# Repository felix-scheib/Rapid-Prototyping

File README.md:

# Rapid Prototyping

This is the repository with my prototype of [Rapid Prototyping](https://obs.fbi.h-da.de/mhb/modul.php?nr=30.2670&sem=20231) by [Prof. Dr. Stefan Rapp](https://fbi.h-da.de/personen/stefan-rapp/) in the winterterm 23/24.

The following tools are used to create the prototype:

- [PlatformIO](https://platformio.org/)
- [KiCad](https://www.kicad.org/)
- [FreeCAD](https://www.freecad.org/)

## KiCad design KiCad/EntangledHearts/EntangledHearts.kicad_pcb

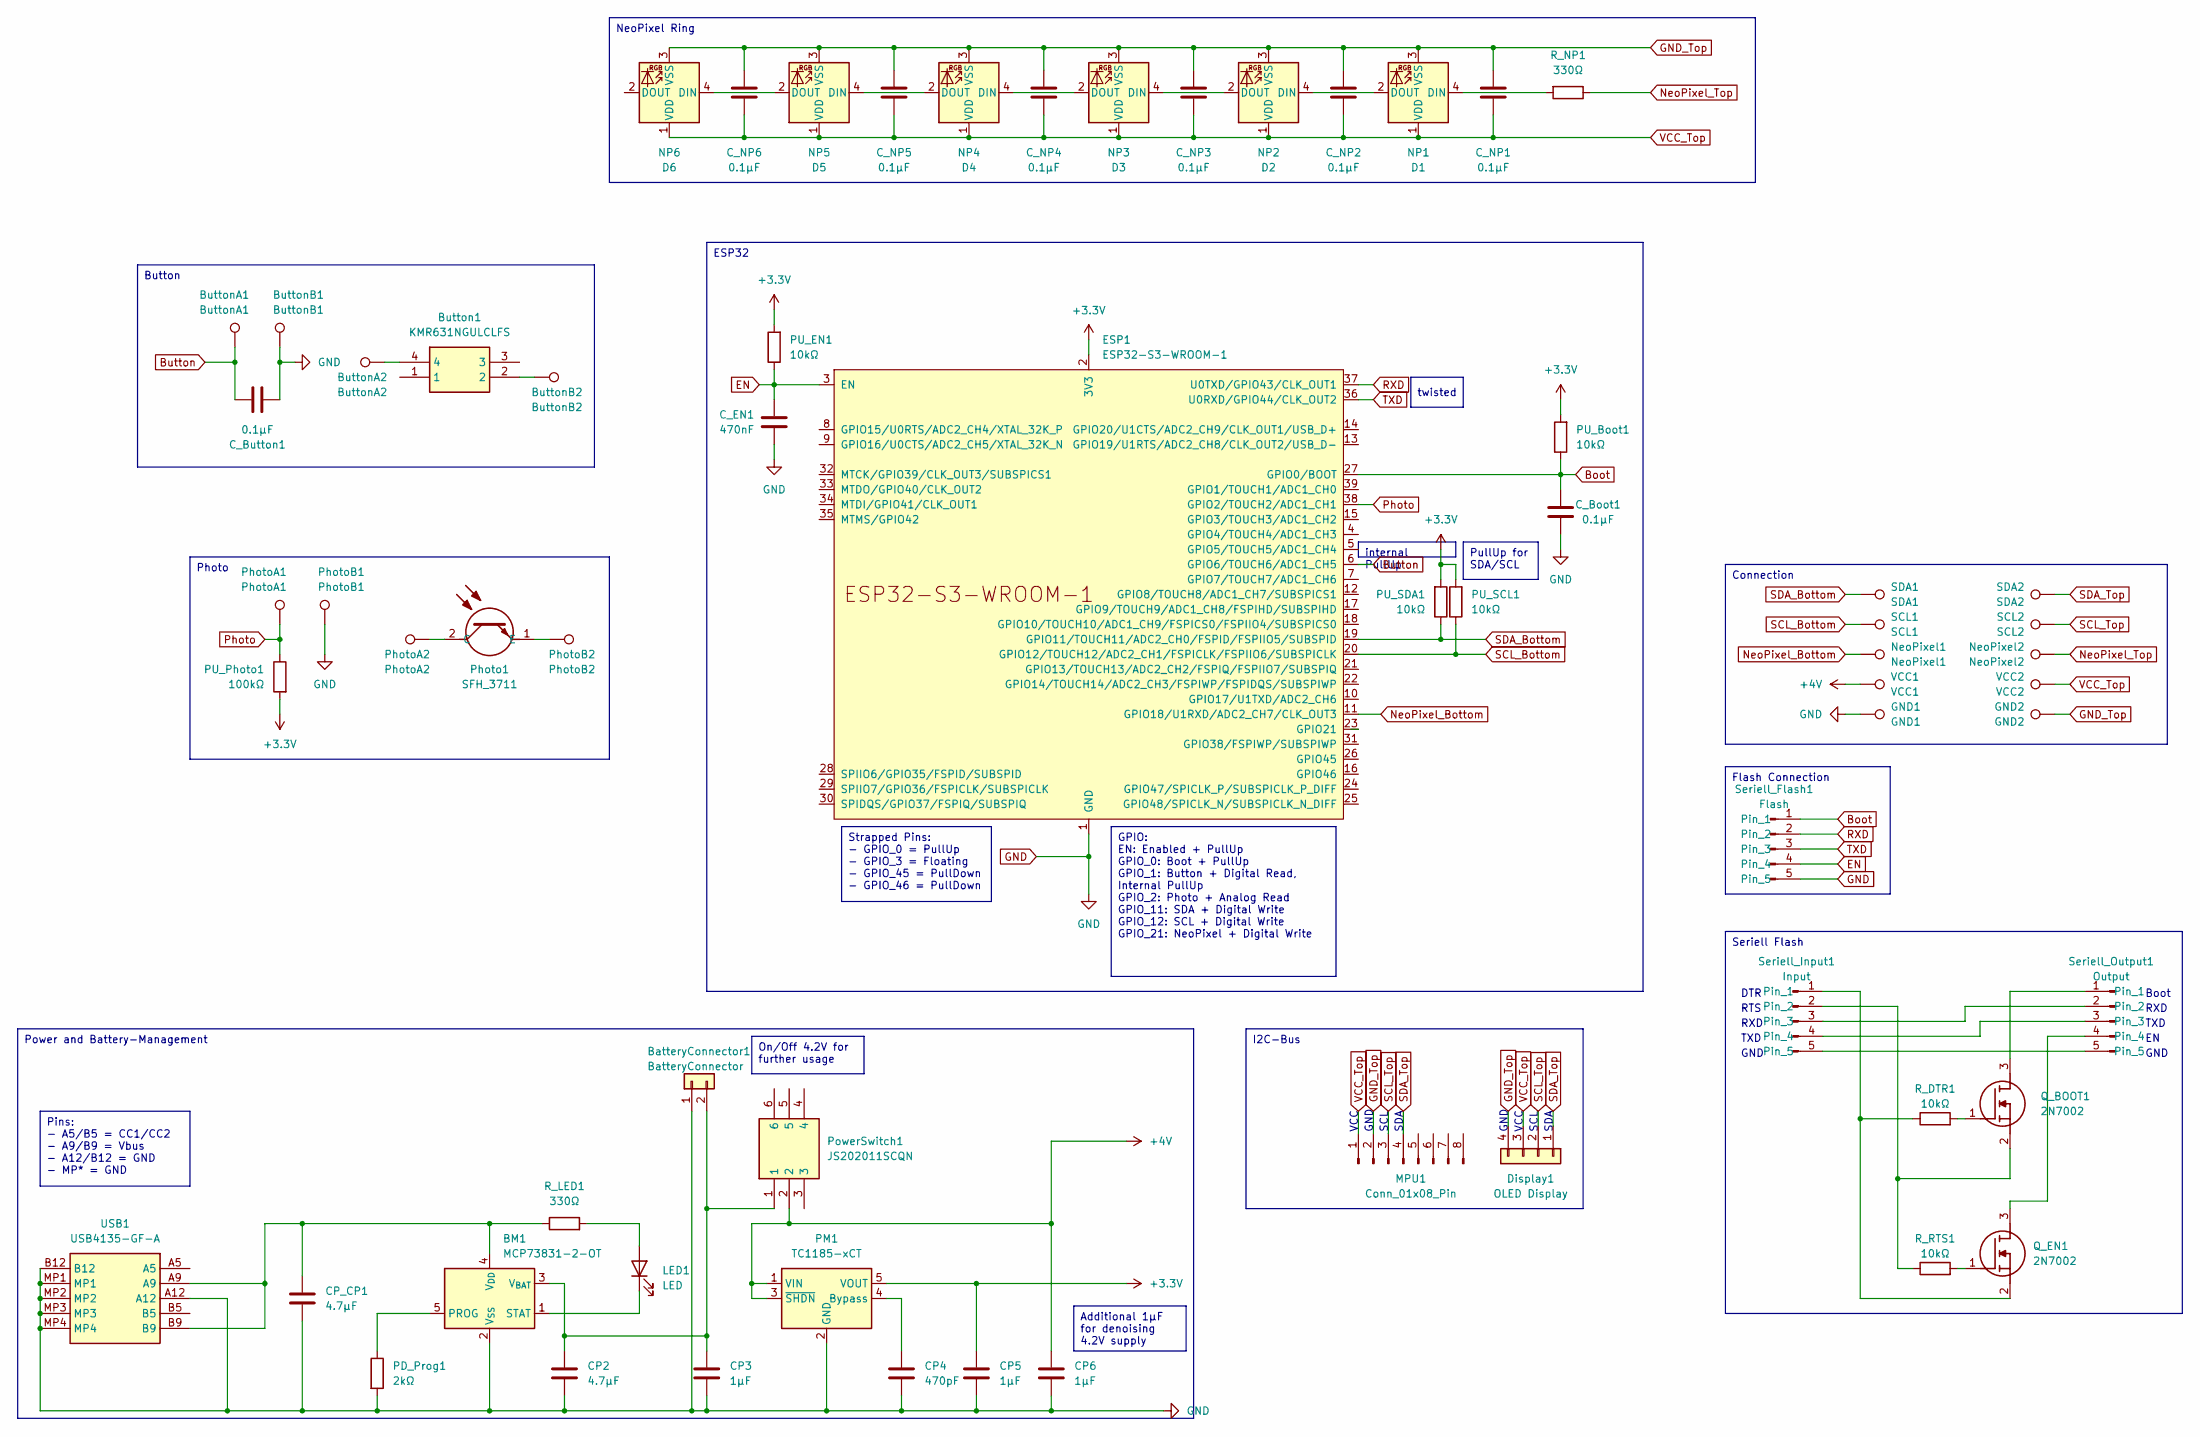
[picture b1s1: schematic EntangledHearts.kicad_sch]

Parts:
BM1: MCP73831-2-OT; SOT-23-5
BatteryConnector1: BatteryConnector; JST_PH_S2B-PH-SM4-TB_1x02-1MP_P2.00mm_Horizontal
Button1: KMR631NGULCLFS; KMR621NG; Mouser Part Number 611-KMR631NGULCLFS
ButtonA1: ButtonA1; TestPoint_Pad_1.5x1.5mm
ButtonA2: ButtonA2; TestPoint_Pad_1.5x1.5mm
ButtonB1: ButtonB1; TestPoint_Pad_1.5x1.5mm
ButtonB2: ButtonB2; TestPoint_Pad_1.5x1.5mm
CP2: 4.7µF; C_0805_2012Metric
CP3, CP5, CP6: 1µF; C_0805_2012Metric
CP4: 470pF; C_0805_2012Metric
CP_CP1: 4.7µF; C_0805_2012Metric
C_Boot1: 0.1µF; C_0805_2012Metric
C_Button1: 0.1µF; C_0805_2012Metric
C_EN1: 470nF; C_0805_2012Metric
C_NP1, C_NP2, C_NP3, C_NP4, C_NP5, C_NP6: 0.1µF; C_0805_2012Metric
D1: NP1; LED_WS2812B_PLCC4_5.0x5.0mm_P3.2mm
D2: NP2; LED_WS2812B_PLCC4_5.0x5.0mm_P3.2mm
D3: NP3; LED_WS2812B_PLCC4_5.0x5.0mm_P3.2mm
D4: NP4; LED_WS2812B_PLCC4_5.0x5.0mm_P3.2mm
D5: NP5; LED_WS2812B_PLCC4_5.0x5.0mm_P3.2mm
D6: NP6; LED_WS2812B_PLCC4_5.0x5.0mm_P3.2mm
Display1: OLED Display; PinHeader_1x04_P2.54mm_Vertical
ESP1: ESP32-S3-WROOM-1
GND1: GND1; TestPoint_Pad_1.5x1.5mm
GND2: GND2; TestPoint_Pad_1.5x1.5mm
LED1: LED; LED_0805_2012Metric
MPU1: Conn_01x08_Pin; PinHeader_1x08_P2.54mm_Vertical_SMD_Pin1Left
NeoPixel1: NeoPixel1; TestPoint_Pad_1.5x1.5mm
NeoPixel2: NeoPixel2; TestPoint_Pad_1.5x1.5mm
PD_Prog1: 2kΩ; R_0805_2012Metric
PM1: TC1185-xCT; SOT-23-5
PU_Boot1: 10kΩ; R_0805_2012Metric
PU_EN1: 10kΩ; R_0805_2012Metric
PU_Photo1: 100kΩ; R_0805_2012Metric
PU_SCL1: 10kΩ; R_0805_2012Metric
PU_SDA1: 10kΩ; R_0805_2012Metric
Photo1: SFH_3711; SFH3711; Mouser Part Number 720-SFH3711
PhotoA1: PhotoA1; TestPoint_Pad_1.5x1.5mm
PhotoA2: PhotoA2; TestPoint_Pad_1.5x1.5mm
PhotoB1: PhotoB1; TestPoint_Pad_1.5x1.5mm
PhotoB2: PhotoB2; TestPoint_Pad_1.5x1.5mm
PowerSwitch1: JS202011SCQN; Mouser Part Number 611-JS202011SCQN
Q_BOOT1: 2N7002; SOT96P240X120-3N; Manufacturer_Part_Number 2N7002; Mouser Part Number 512-2N7002
Q_EN1: 2N7002; SOT96P240X120-3N; Manufacturer_Part_Number 2N7002; Mouser Part Number 512-2N7002
R_DTR1: 10kΩ; R_0805_2012Metric
R_LED1: 330Ω; R_0805_2012Metric
R_NP1: 330Ω; R_0805_2012Metric
R_RTS1: 10kΩ; R_0805_2012Metric
SCL1: SCL1; TestPoint_Pad_1.5x1.5mm
SCL2: SCL2; TestPoint_Pad_1.5x1.5mm
SDA1: SDA1; TestPoint_Pad_1.5x1.5mm
SDA2: SDA2; TestPoint_Pad_1.5x1.5mm
Seriell_Flash1: Flash; PinHeader_1x05_P2.54mm_Vertical_SMD_Pin1Left
Seriell_Input1: Input; PinHeader_1x05_P2.54mm_Vertical_SMD_Pin1Left
Seriell_Output1: Output; PinHeader_1x05_P2.54mm_Vertical_SMD_Pin1Left
USB1: USB4135-GF-A; USB4135GFA; Mouser Part Number 640-USB4135-GF-A
VCC1: VCC1; TestPoint_Pad_1.5x1.5mm
VCC2: VCC2; TestPoint_Pad_1.5x1.5mm

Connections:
+3.3V: CP5.1, ESP1.2 (3V3), PM1.5 (VOUT), PU_Boot1.2, PU_EN1.2, PU_Photo1.2, PU_SCL1.2, PU_SDA1.2
+4V: CP6.1, PM1.1 (VIN), PM1.3 (~SHDN), PowerSwitch1.2, VCC1.1
Boot: C_Boot1.2, ESP1.27 (GPIO0/BOOT), PU_Boot1.1, Seriell_Flash1.1
Button: ButtonA1.1, C_Button1.1, ESP1.6 (GPIO6/TOUCH6/ADC1_CH5)
EN: C_EN1.2, ESP1.3 (EN), PU_EN1.1, Seriell_Flash1.4
GND: BM1.2 (V_{SS}), BatteryConnector1.1, ButtonB1.1, CP2.2, CP3.2, CP4.2, CP5.2, CP6.2, CP_CP1.2, C_Boot1.1, C_Button1.2, C_EN1.1, ESP1.1 (GND), ESP1.40 (GND), ESP1.41 (GND), GND1.1, PD_Prog1.2, PM1.2 (GND), PhotoB1.1, Seriell_Flash1.5, USB1.A12, USB1.B12, USB1.MP1, USB1.MP2, USB1.MP3, USB1.MP4
GND_Top: C_NP1.2, C_NP2.2, C_NP3.2, C_NP4.2, C_NP5.2, C_NP6.2, D1.3 (VSS), D2.3 (VSS), D3.3 (VSS), D4.3 (VSS), D5.3 (VSS), D6.3 (VSS), Display1.4, GND2.1, MPU1.2
NeoPixel_Bottom: ESP1.11 (GPIO18/U1RXD/ADC2_CH7/CLK_OUT3), NeoPixel1.1
NeoPixel_Top: NeoPixel2.1, R_NP1.1
unnamed: BM1.5 (PROG), PD_Prog1.1
unnamed: BM1.1 (STAT), LED1.1 (K)
unnamed: BM1.3 (V_{BAT}), BatteryConnector1.2, CP2.1, CP3.1, PowerSwitch1.1
unnamed: BM1.4 (V_{DD}), CP_CP1.1, R_LED1.1, USB1.A9, USB1.B9
unnamed: Button1.2, ButtonB2.1
unnamed: Button1.4, ButtonA2.1
unnamed: D1.4 (DIN), R_NP1.2
unnamed: D1.2 (DOUT), D2.4 (DIN)
unnamed: D2.2 (DOUT), D3.4 (DIN)
unnamed: D3.2 (DOUT), D4.4 (DIN)
unnamed: D4.2 (DOUT), D5.4 (DIN)
unnamed: D5.2 (DOUT), D6.4 (DIN)
unnamed: LED1.2 (A), R_LED1.2
unnamed: CP4.1, PM1.4 (Bypass)
unnamed: Photo1.2 (C), PhotoA2.1
unnamed: Photo1.1 (E), PhotoB2.1
unnamed: Q_BOOT1.3 (D), Seriell_Output1.1
unnamed: Q_BOOT1.1 (G), R_DTR1.2
unnamed: Q_BOOT1.2 (S), R_RTS1.1, Seriell_Input1.2
unnamed: Q_EN1.3 (D), Seriell_Output1.4
unnamed: Q_EN1.1 (G), R_RTS1.2
unnamed: Q_EN1.2 (S), R_DTR1.1, Seriell_Input1.1
unnamed: Seriell_Input1.3, Seriell_Output1.2
unnamed: Seriell_Input1.4, Seriell_Output1.3
unnamed: Seriell_Input1.5, Seriell_Output1.5
Photo: ESP1.38 (GPIO2/TOUCH2/ADC1_CH1), PU_Photo1.1, PhotoA1.1
RXD: ESP1.37 (U0TXD/GPIO43/CLK_OUT1), Seriell_Flash1.2
SCL_Bottom: ESP1.20 (GPIO12/TOUCH12/ADC2_CH1/FSPICLK/FSPIIO6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), PU_SCL1.1, SCL1.1
SCL_Top: Display1.2, MPU1.3, SCL2.1
SDA_Bottom: ESP1.19 (GPIO11/TOUCH11/ADC2_CH0/FSPID/FSPIIO5/S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), PU_SDA1.1, SDA1.1
SDA_Top: Display1.1, MPU1.4, SDA2.1
TXD: ESP1.36 (U0RXD/GPIO44/CLK_OUT2), Seriell_Flash1.3
VCC_Top: C_NP1.1, C_NP2.1, C_NP3.1, C_NP4.1, C_NP5.1, C_NP6.1, D1.1 (VDD), D2.1 (VDD), D3.1 (VDD), D4.1 (VDD), D5.1 (VDD), D6.1 (VDD), Display1.3, MPU1.1, VCC2.1

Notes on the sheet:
Additional 1µF for denoising 4.2V supply
Pins: - A5/B5 = CC1/CC2 - A9/B9 = Vbus - A12/B12 = GND - MP* = GND
On/Off 4.2V for further usage
Power and Battery-Management
Photo
I2C-Bus
ESP32
internal PullUp
PullUp for SDA/SCL
GPIO: EN: Enabled + PullUp GPIO_0: Boot + PullUp GPIO_1: Button + Digital Read, Internal PullUp GPIO_2: Photo + Analog Read GPIO_11: SDA + Digital Write GPIO_12: SCL + Digital Write GPIO_21: NeoPixel + Digital Write
Flash Connection
twisted
Seriell Flash
Connection
Strapped Pins: - GPIO_0 = PullUp - GPIO_3 = Floating - GPIO_45 = PullDown - GPIO_46 = PullDown
Button
NeoPixel Ring
TXD
SCL
GND
RXD
VCC
DTR
SDA
RTS
Boot

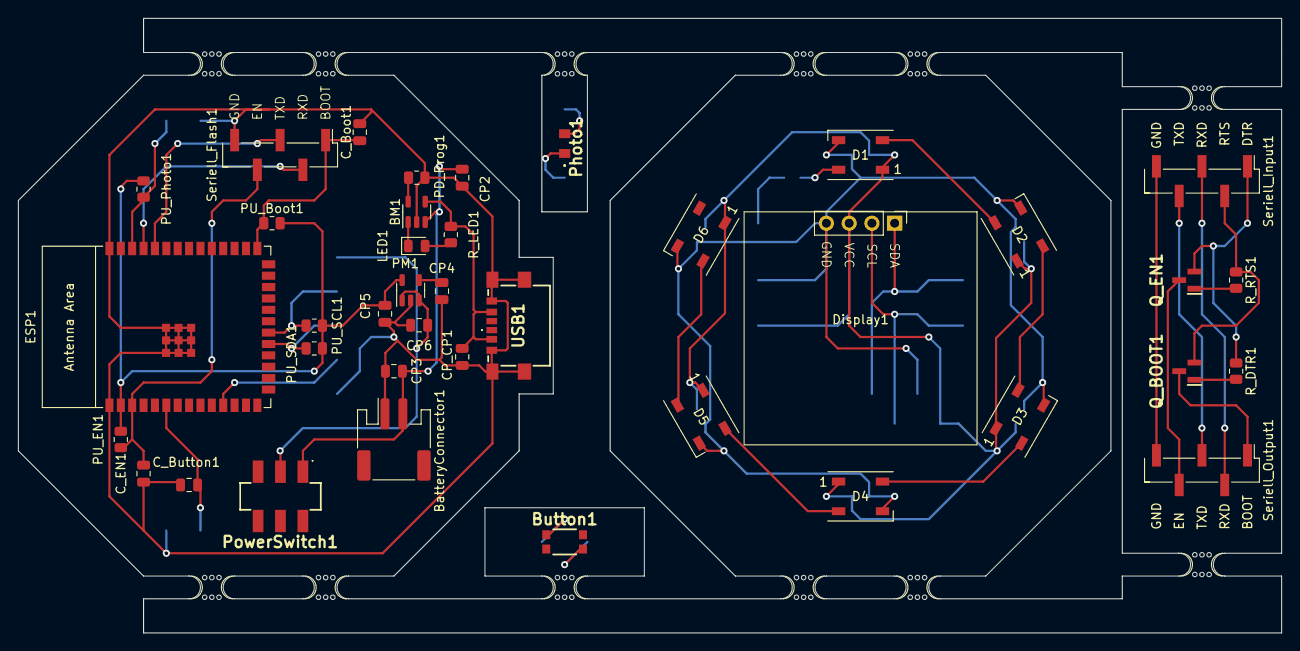
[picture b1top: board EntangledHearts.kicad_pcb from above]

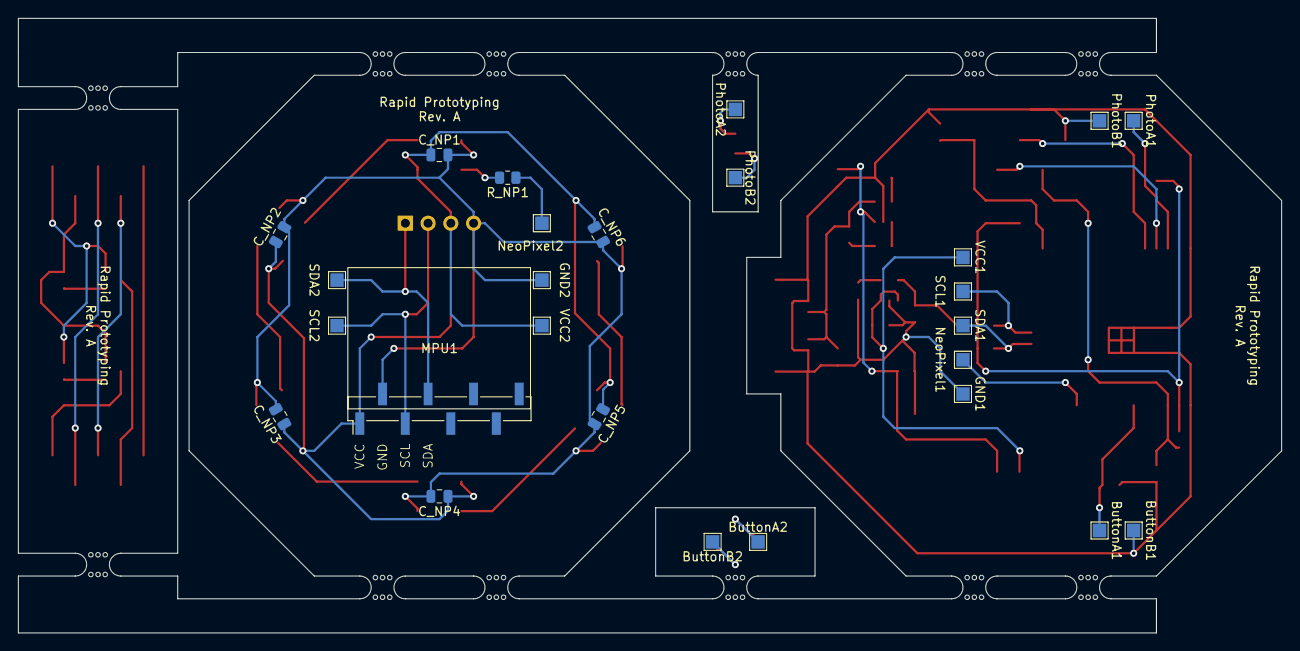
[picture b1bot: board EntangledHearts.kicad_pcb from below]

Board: 2 copper layers, 141.0 x 68.6 mm, 77 parts (26 on the bottom side), 42 nets.

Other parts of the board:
mouse-bite-2.54mm-slot, mouse-bite-2.54mm-slot#2, mouse-bite-2.54mm-slot#3, mouse-bite-2.54mm-slot#4, mouse-bite-2.54mm-slot#5, mouse-bite-2.54mm-slot#6, mouse-bite-2.54mm-slot#7, mouse-bite-2.54mm-slot#8, mouse-bite-2.54mm-slot#9, mouse-bite-2.54mm-slot#10, mouse-bite-2.54mm-slot#11, mouse-bite-2.54mm-slot#12: VAL**; mouse-bite-2.54mm-slot

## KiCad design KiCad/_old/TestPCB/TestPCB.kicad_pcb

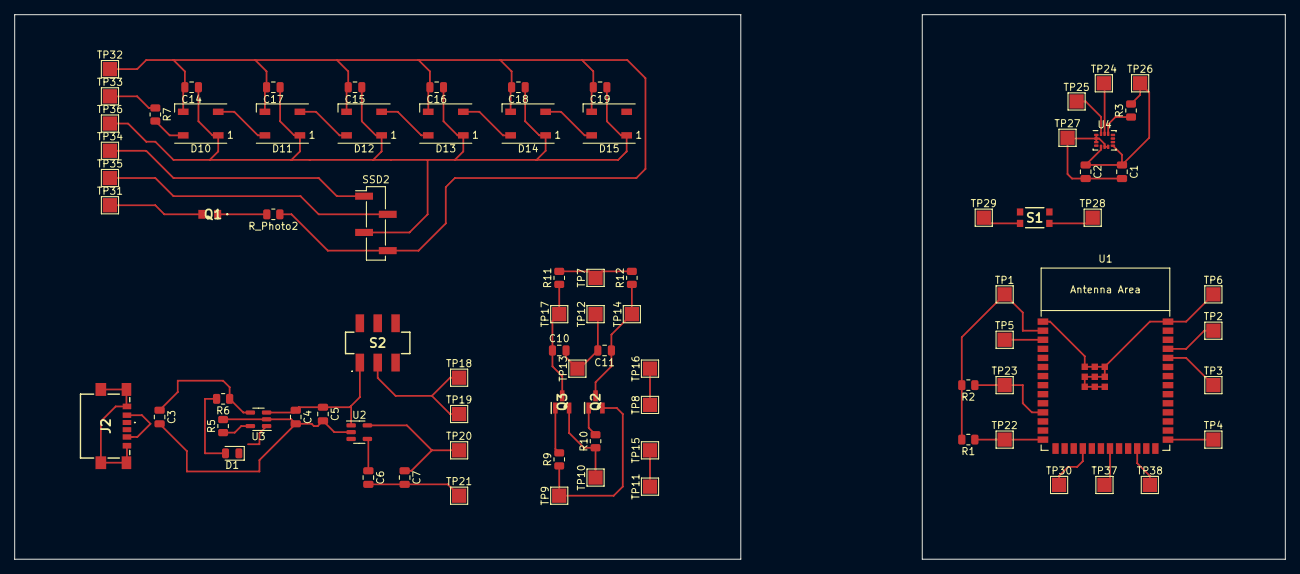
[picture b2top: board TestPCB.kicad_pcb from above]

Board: 2 copper layers, 177.8 x 76.2 mm, 82 parts (0 on the bottom side), 50 nets.

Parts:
C1, C2: 100nF; C_0805_2012Metric
C3, C4: 4.7µF; C_0805_2012Metric
C5, C7: 1µF; C_0805_2012Metric
C6: 470pF; C_0805_2012Metric
C10, C14, C15, C16, C17, C18, C19: 0.1µF; C_0805_2012Metric
C11: 470nF; C_0805_2012Metric
D1: LED; LED_0805_2012Metric
D10, D11, D12, D13, D14, D15: WS2812B; LED_WS2812B_PLCC4_5.0x5.0mm_P3.2mm
J2: USB4135-GF-A; USB4135GFA
Q1: SFH_3711; SFH3711
Q2, Q3: 2N7002; SOT96P240X120-3N
R1, R2, R3, R9, R10, R11, R12: 10kΩ; R_0805_2012Metric
R5: 2kΩ; R_0805_2012Metric
R6, R7: 330Ω; R_0805_2012Metric
R_Photo2: 0Ω; R_0805_2012Metric
S1: KMR631NGULCLFS; KMR621NG
S2: JS202011SCQN
SSD2: Conn_01x04_Pin; PinHeader_1x04_P2.54mm_Vertical_SMD_Pin1Left
TP1, TP7, TP20, TP26: +3.3V; TestPoint_Pad_2.0x2.0mm
TP2, TP15: FL_RXD; TestPoint_Pad_2.0x2.0mm
TP3, TP16: FL_TXD; TestPoint_Pad_2.0x2.0mm
TP4, TP17: FL_RST; TestPoint_Pad_2.0x2.0mm
TP5, TP14: FL_EN; TestPoint_Pad_2.0x2.0mm
TP6, TP12, TP13, TP21, TP27, TP28, TP32: GND; TestPoint_Pad_2.0x2.0mm
TP8: TXD; TestPoint_Pad_2.0x2.0mm
TP9: DTR; TestPoint_Pad_2.0x2.0mm
TP10: RTS; TestPoint_Pad_2.0x2.0mm
TP11: RXD; TestPoint_Pad_2.0x2.0mm
TP18: +4.2V; TestPoint_Pad_2.0x2.0mm
TP19: VBat; TestPoint_Pad_2.0x2.0mm
TP22, TP24, TP35: SCL; TestPoint_Pad_2.0x2.0mm
TP23, TP25, TP34: SDA; TestPoint_Pad_2.0x2.0mm
TP29, TP30: GPIO_Switch; TestPoint_Pad_2.0x2.0mm
TP31, TP37: GPIO_Photo; TestPoint_Pad_2.0x2.0mm
TP33, TP38: GPIO_Pixel; TestPoint_Pad_2.0x2.0mm
TP36: +4.4V; TestPoint_Pad_2.0x2.0mm
U1: ESP32-S3-WROOM-1
U2: TC1185-xCT; SOT-23-5
U3: MCP73831-2-OT; SOT-23-5
U4: LSM6DSM; LGA-14_3x2.5mm_P0.5mm_LayoutBorder3x4y

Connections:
unnamed: C10.2, C11.2, TP12.1, TP13.1
unnamed: D1.2 (A), R6.2
unnamed: D1.1 (K), U3.1 (STAT)
unnamed: D10.4 (DIN), R7.2
unnamed: D10.2 (DOUT), D11.4 (DIN)
unnamed: C14.1, C15.1, C16.1, C17.1, C18.1, C19.1, D10.1 (VDD), D11.1 (VDD), D12.1 (VDD), D13.1 (VDD), D14.1 (VDD), D15.1 (VDD), SSD2.3, TP36.1
unnamed: C14.2, C15.2, C16.2, C17.2, C18.2, C19.2, D10.3 (VSS), D11.3 (VSS), D12.3 (VSS), D13.3 (VSS), D14.3 (VSS), D15.3 (VSS), R_Photo2.1, SSD2.4, TP32.1
unnamed: D11.2 (DOUT), D12.4 (DIN)
unnamed: D12.2 (DOUT), D13.4 (DIN)
unnamed: D13.2 (DOUT), D14.4 (DIN)
unnamed: D14.2 (DOUT), D15.4 (DIN)
unnamed: Q1.2 (C), TP31.1
unnamed: Q1.1 (E), R_Photo2.2
unnamed: C11.1, Q2.3 (D), R12.1, TP14.1
unnamed: Q2.1 (G), R10.2
unnamed: Q2.2 (S), R9.1, TP9.1
unnamed: C10.1, Q3.3 (D), R11.1, TP17.1
unnamed: Q3.1 (G), R9.2
unnamed: Q3.2 (S), R10.1, TP10.1
unnamed: R7.1, TP33.1
unnamed: R11.2, R12.2, TP7.1
unnamed: S1.1, TP29.1
unnamed: S1.2, TP28.1
unnamed: S2.2, TP18.1, TP19.1
unnamed: SSD2.1, TP34.1
unnamed: SSD2.2, TP35.1
unnamed: TP6.1, U1.1 (GND), U1.40 (GND), U1.41 (GND)
unnamed: TP11.1, TP15.1
unnamed: TP8.1, TP16.1
unnamed: R1.2, R2.2, TP1.1, U1.2 (3V3)
unnamed: TP5.1, U1.3 (EN)
unnamed: TP4.1, U1.27 (GPIO0/BOOT)
unnamed: TP30.1, U1.18 (GPIO10/TOUCH10/ADC1_CH9/FSPICS0/FSPIIO4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)
unnamed: TP37.1, U1.21 (GPIO13/TOUCH13/ADC2_CH2/FSPIQ/FSPIIO7/S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)
unnamed: R2.1, TP23.1, U1.11 (GPIO18/U1RXD/ADC2_CH7/CLK_OUT3)
unnamed: R1.1, TP22.1, U1.14 (GPIO20/U1CTS/ADC2_CH9/CLK_OUT1/USB_D+)
unnamed: TP38.1, U1.24 (GPIO47/SPICLK_P/SUBSPICLK_P_DIFF)
unnamed: TP3.1, U1.36 (U0RXD/GPIO44/CLK_OUT2)
unnamed: TP2.1, U1.37 (U0TXD/GPIO43/CLK_OUT1)
unnamed: C6.1, U2.4 (Bypass)
unnamed: C3.2, C4.2, C5.2, C6.2, C7.2, J2.A12, J2.B12, J2.MP1, J2.MP2, J2.MP3, J2.MP4, R5.2, TP21.1, U2.2 (GND), U3.2 (V_{SS})
unnamed: C4.1, C5.1, S2.1, U2.1 (VIN), U2.3 (~SHDN), U3.3 (V_{BAT})
unnamed: C7.1, TP20.1, U2.5 (VOUT)
unnamed: R5.1, U3.5 (PROG)
unnamed: C3.1, J2.A9, J2.B9, R6.1, U3.4 (V_{DD})
unnamed: R3.1, U4.12 (CS)
unnamed: TP24.1, U4.13 (SCL)
unnamed: C1.2, C2.2, TP27.1, U4.1 (SDO/SA0), U4.2 (SDX), U4.3 (SCX), U4.6 (GND), U4.7 (GND)
unnamed: TP25.1, U4.14 (SDA)
unnamed: C1.1, C2.1, R3.2, TP26.1, U4.5 (VDDIO), U4.8 (VDD)

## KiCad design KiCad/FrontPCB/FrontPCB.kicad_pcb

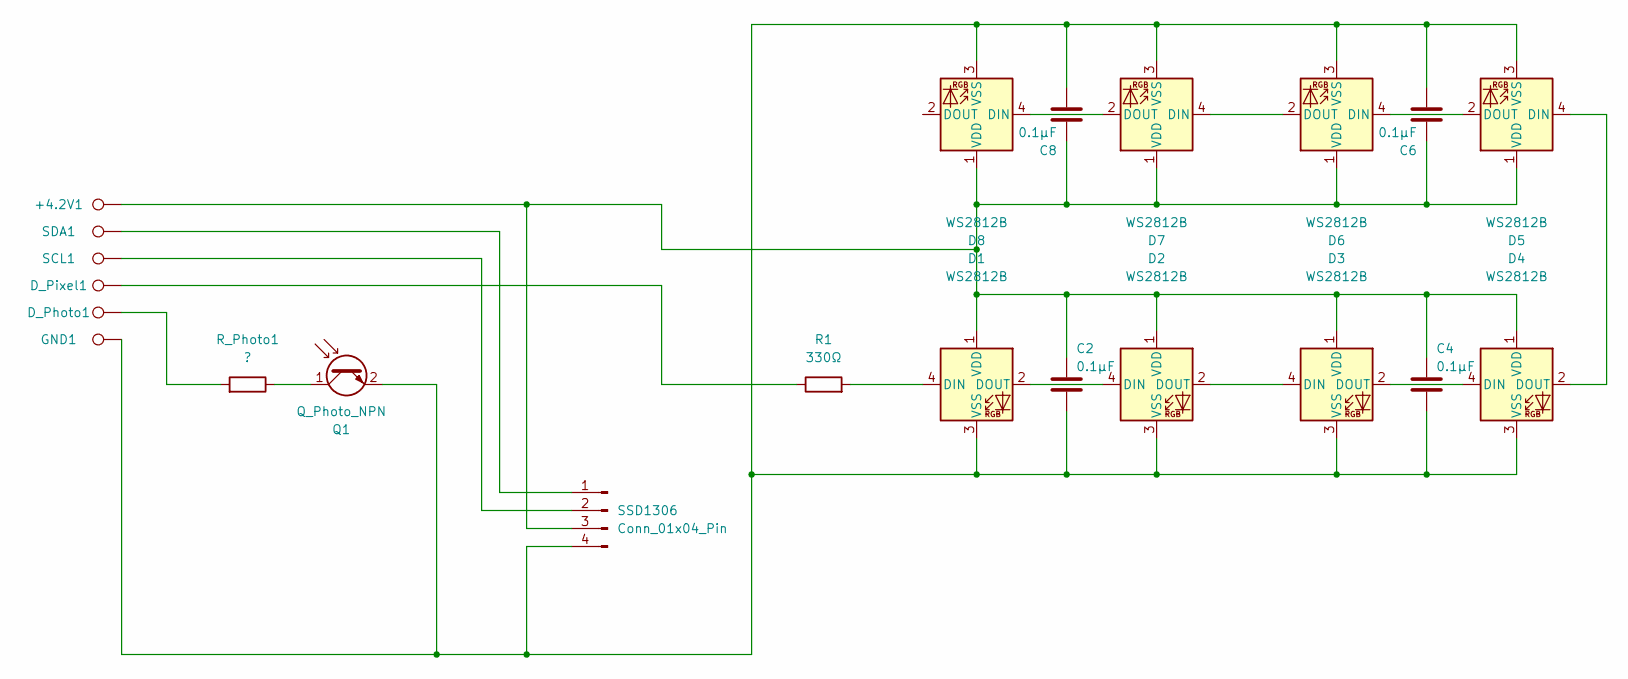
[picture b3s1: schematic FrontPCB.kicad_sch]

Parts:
+4.2V1: TestPoint; TestPoint_Pad_2.0x2.0mm
C2, C4, C6, C8: 0.1µF; C_0805_2012Metric
D1, D2, D3, D4, D5, D6, D7, D8: WS2812B; LED_WS2812B_PLCC4_5.0x5.0mm_P3.2mm
D_Photo1: TestPoint; TestPoint_Pad_2.0x2.0mm
D_Pixel1: TestPoint; TestPoint_Pad_2.0x2.0mm
GND1: TestPoint; TestPoint_Pad_2.0x2.0mm
Q1: Q_Photo_NPN; LED_0805_2012Metric
R1: 330Ω; R_0805_2012Metric
R_Photo1: ?; R_0805_2012Metric
SCL1: TestPoint; TestPoint_Pad_2.0x2.0mm
SDA1: TestPoint; TestPoint_Pad_2.0x2.0mm
SSD1306: Conn_01x04_Pin; PinHeader_1x04_P2.54mm_Vertical_SMD_Pin1Left

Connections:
unnamed: D1.4 (DIN), R1.2
unnamed: D1.2 (DOUT), D2.4 (DIN)
unnamed: +4.2V1.1, C2.1, C4.1, C6.1, C8.1, D1.1 (VDD), D2.1 (VDD), D3.1 (VDD), D4.1 (VDD), D5.1 (VDD), D6.1 (VDD), D7.1 (VDD), D8.1 (VDD), SSD1306.3
unnamed: C2.2, C4.2, C6.2, C8.2, D1.3 (VSS), D2.3 (VSS), D3.3 (VSS), D4.3 (VSS), D5.3 (VSS), D6.3 (VSS), D7.3 (VSS), D8.3 (VSS), GND1.1, Q1.2 (E), SSD1306.4
unnamed: D2.2 (DOUT), D3.4 (DIN)
unnamed: D3.2 (DOUT), D4.4 (DIN)
unnamed: D4.2 (DOUT), D5.4 (DIN)
unnamed: D5.2 (DOUT), D6.4 (DIN)
unnamed: D6.2 (DOUT), D7.4 (DIN)
unnamed: D7.2 (DOUT), D8.4 (DIN)
unnamed: D_Photo1.1, R_Photo1.2
unnamed: D_Pixel1.1, R1.1
unnamed: Q1.1 (C), R_Photo1.1
unnamed: SDA1.1, SSD1306.1
unnamed: SCL1.1, SSD1306.2

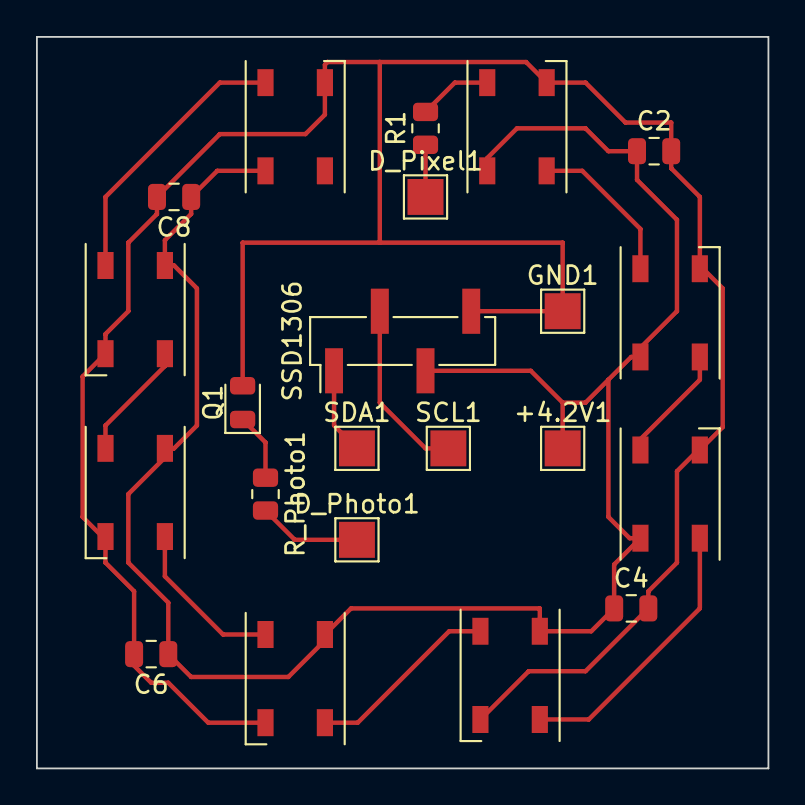
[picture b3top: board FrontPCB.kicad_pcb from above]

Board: 2 copper layers, 40.6 x 40.6 mm, 22 parts (0 on the bottom side), 15 nets.

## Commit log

2023-11-27 ADD: .gitgnore added
2023-11-27 ADD: PlatformIO project initialized
2023-11-27 CHG: .gitignore modified
2023-11-27 ADD: MQTT implemented
2023-11-27 ADD: led-stripe added
2023-11-28 ADD: added credentials.h template
2023-11-28 DEL: credentials.h deleted
2023-11-28 ADD: added credentials information in README.md
2023-11-29 ADD: KiCad project initialized
2023-11-29 ADD: basic PCB-Layout added
2023-12-06 CHG: minor changes to PCB
2023-12-06 ADD: right NeoPixel version added
2023-12-06 ADD: PCB for NeoPixels started
2023-12-06 CHG: changed name to FrontPCB
2023-12-06 FIX: fixed missing .kicad_sch files
2023-12-06 CHG: changed wiring of front PCB
2023-12-11 CHG: components of FrontPCB added
2023-12-11 ADD: started with BackPCB
2023-12-12 ADD: charge and flash circuits designed
2023-12-12 ADD: all circuits added
2023-12-12 ADD: PCB added
2023-12-12 ADD: PCB connections finished
2023-12-13 ADD: parts arranged in two pcbs
2023-12-13 ADD: 3D-Modell for switch added
2023-12-13 CHG: resized textes
2023-12-13 CHG: files renamed
2023-12-13 CHG: cleanub of vias
2023-12-13 ADD: Gerber-Files added
2023-12-14 CHG: pcb-layouts adopted
2023-12-15 CHG: changes of today
2023-12-21 ADD: new Project initialized
2024-01-06 ADD: schematics for main circuits added
2024-01-08 ADD: all parts added
2024-01-09 ADD: final touches for first plot
2024-01-18 CHG: GPIO photo low-active
2024-01-25 DEL: *.lck files removed
2024-01-25 CHG: new MOSFET-Footprint added
2024-01-27 ADD: flashing circuit added
2024-01-29 ADD: all footprints added
2024-02-02 ADD: first pcbs added
2024-02-07 CHG cleanup of Schematics done
2024-02-07 ADD: further progress
2024-02-08 CHG: some minor changes
2024-02-09 ADD: all parts connected
2024-02-09 ADD: all errors in PCB fixed
2024-02-09 ADD: 3D-File for connector added
2024-02-11 CHG: rewiring of front pcb
2024-02-11 ADD: all components on front PCB placed
2024-02-11 ADD: all components connected
2024-02-11 CHG: Alignment changed
2024-02-11 ADD: mousebites added
2024-02-12 ADD: Gerberfiles added
2024-02-24 DEL: removed KiCad/_old/
2024-02-24 ADD: initialized PlatformIO project
2024-02-24 ADD: README added
2024-02-24 ADD: Examples for all components added
2024-02-29 CHG: src/main.cpp changed
2024-03-07 ADD: current state added
2024-03-14 ADD: Brocker added
2024-03-14 FIX: wrong path for config fixed
2024-03-14 CHG: hierarchy restructured
2024-03-14 Add: .gitkeeps added
2024-03-14 FIX: mosquitto working on linux now
2024-03-14 CHG: publishing MQTT message on butten-press
2024-03-14 CHG: mosquitto now using host network
2024-03-15 CHG: changed to single MQTT-loop
2024-03-15 CHG: constants changed
2024-03-16 ADD: wrapper for MQTT added
2024-03-16 ADD: simple communication bewtween devices added
2024-03-16 CHG: information to credentials updated
2024-03-17 ADD: First FreeCAD Model added
2024-03-17 ADD: NTP-Time added
2024-03-18 DEL: removed Logger
2024-03-18 CHG: location for credentials.h changed
2024-03-18 ADD: basic display functionality added
2024-03-18 ADD: MQTT Logic added
2024-03-19 ADD: photo-transistor added
2024-03-21 ADD: Support for MPU added
2024-03-23 ADD: Front added
2024-03-24 ADD: Housing finished
2024-03-24 CHG: changed button dimensions
2024-03-24 ADD: files for 3D-printing added
2024-03-25 ADD: Neopixel effects added
2024-03-26 ADD: engraving added
2024-03-28 ADD: presentation added
2024-03-28 ADD: README.md added
2024-03-30 CHG: using NTP-server again
